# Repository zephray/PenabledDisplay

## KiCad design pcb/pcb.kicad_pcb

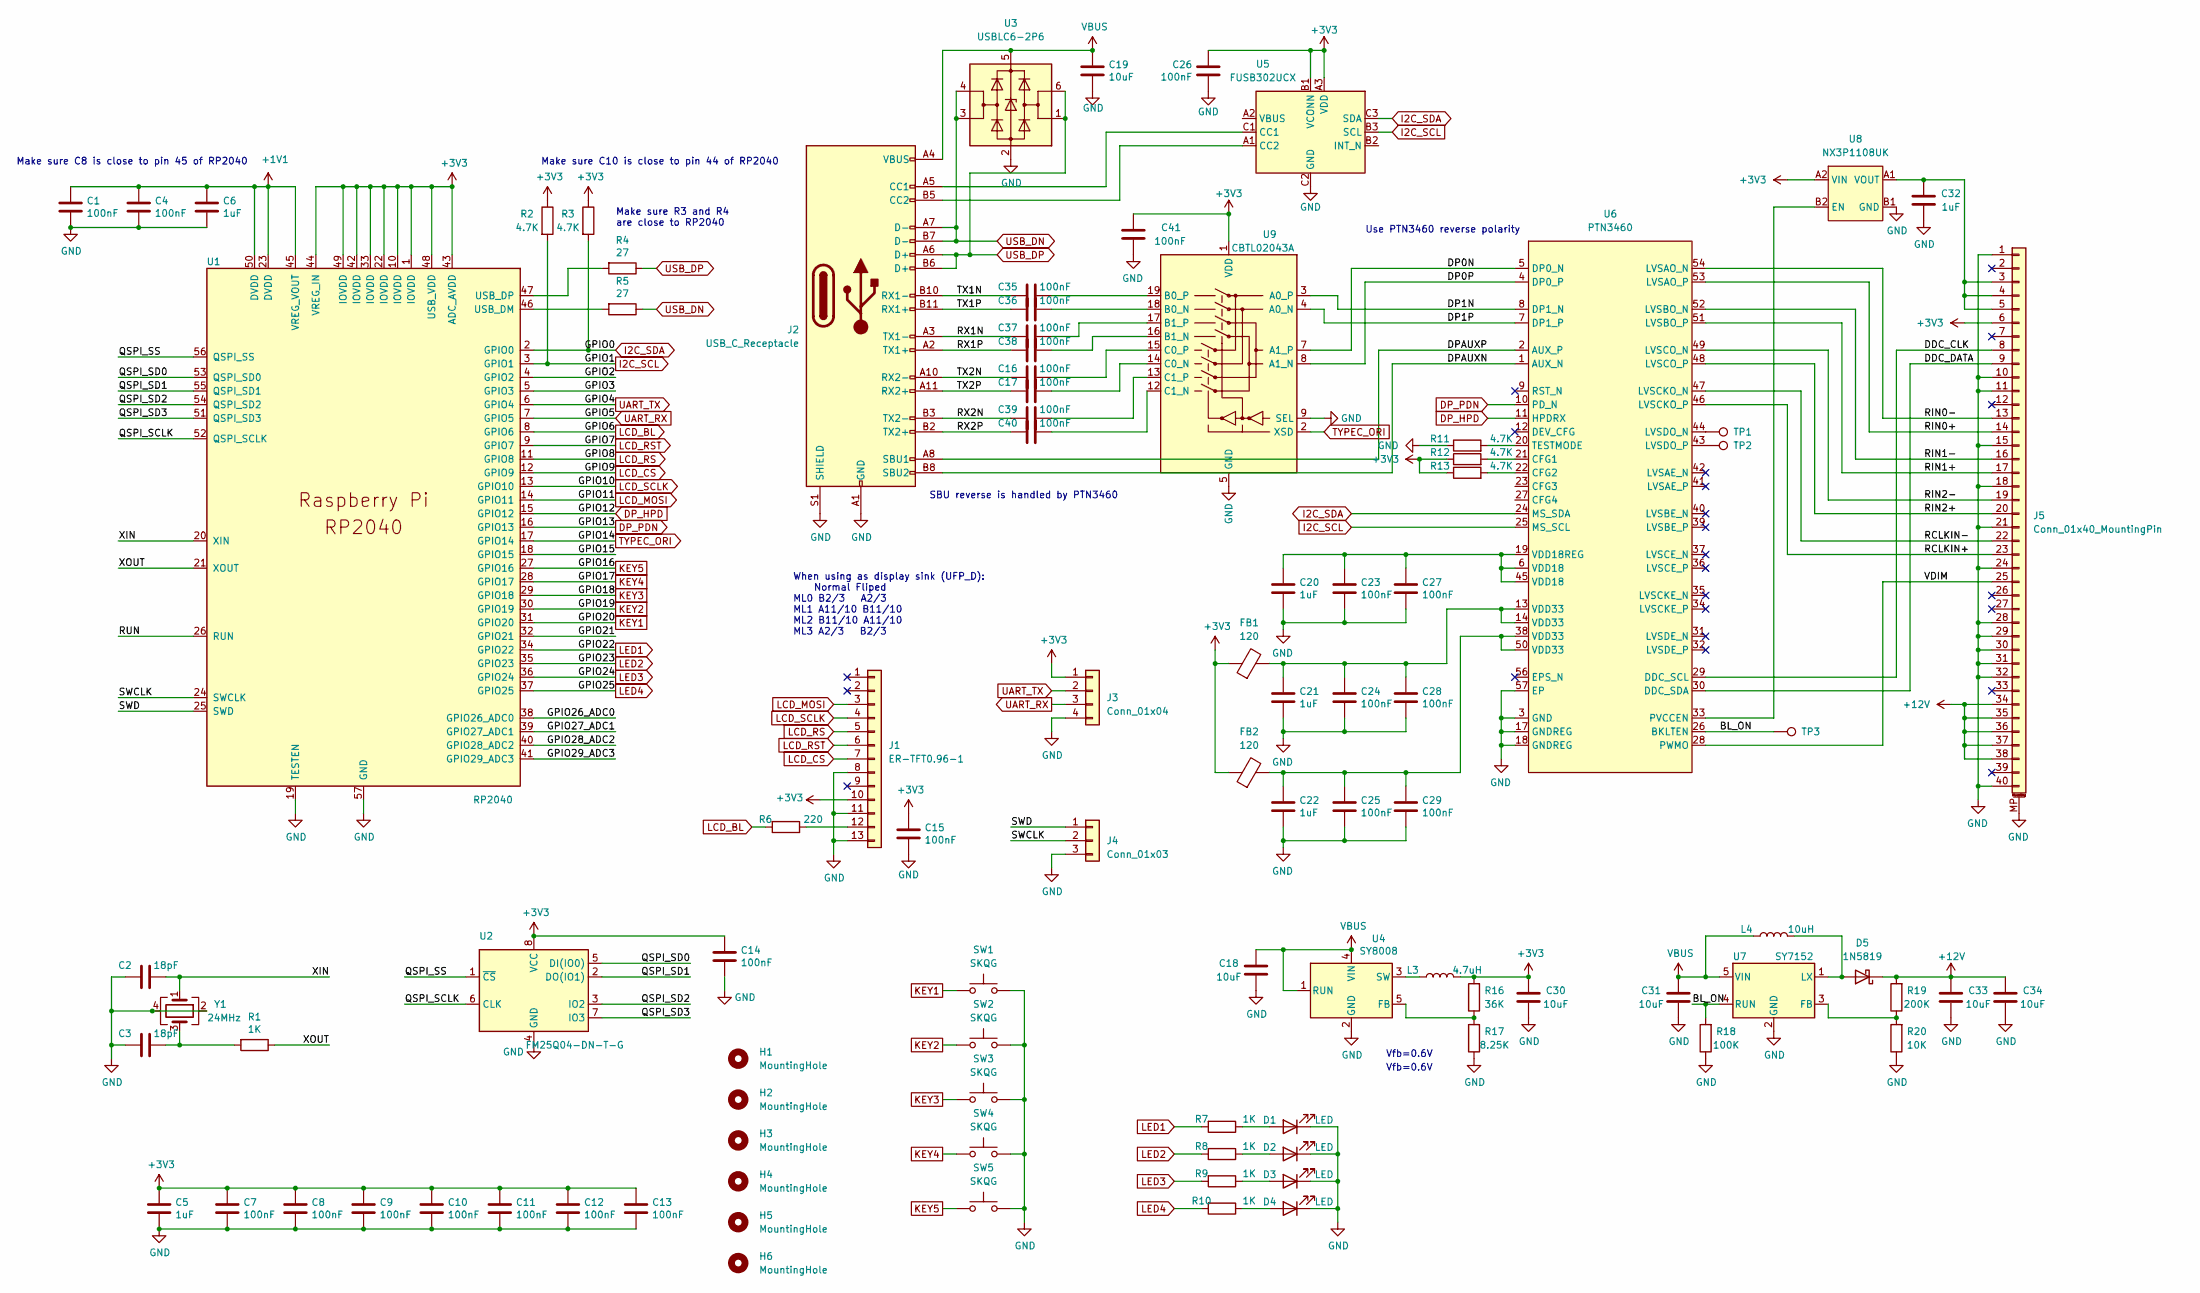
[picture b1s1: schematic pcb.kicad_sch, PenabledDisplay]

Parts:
C1, C4, C7, C8, C9, C10, C11, C12, C13, C14, C15, C16, C17, C23, C24, C25, C26, C27, C28, C29, C35, C36, C37, C38, C39, C40, C41: 100nF; C_0402_1005Metric
C2, C3: 18pF; C_0402_1005Metric
C5, C6, C20, C21, C22, C32: 1uF; C_0402_1005Metric
C18, C19, C30, C31, C33, C34: 10uF; C_0603_1608Metric
D1, D2, D3, D4: LED; LED_0603_1608Metric
D5: 1N5819; D_SOD-123
FB1, FB2: 120; L_0603_1608Metric
H1, H2: MountingHole; MountingHole_2.2mm_M2_DIN965_Pad
H3: MountingHole; MountingHole_2.2mm_M2_DIN965
H4, H5: MountingHole; MountingHole_2.7mm_M2.5_DIN965_Pad
H6: MountingHole; MountingHole_1.7mm
J1: ER-TFT0.96-1; FPC_13_B
J2: USB_C_Receptacle; USB_C_Receptacle_Amphenol_12401548E4-2A
J3: Conn_01x04; PinHeader_1x04_P1.27mm_Vertical
J4: Conn_01x03; PinHeader_1x03_P2.54mm_Vertical
J5: Conn_01x40_MountingPin; Hirose_FH12-40S-0.5SH_1x40-1MP_P0.50mm_Horizontal_Reversed
L3: 4.7uH; L_Vishay_IHLP-1212
L4: 10uH; L_Vishay_IHLP-1616
R1, R7, R8, R9, R10: 1K; R_0402_1005Metric
R2, R3, R11, R12, R13: 4.7K; R_0402_1005Metric
R4, R5: 27; R_0402_1005Metric
R6: 220; R_0402_1005Metric
R16: 36K; R_0402_1005Metric
R17: 8.25K; R_0402_1005Metric
R18: 100K; R_0402_1005Metric
R19: 200K; R_0402_1005Metric
R20: 10K; R_0402_1005Metric
SW1, SW2, SW3, SW4, SW5: SKQG; SW_SPST_SKQG_WithStem
TP1, TP2, TP3: TestPoint; TestPoint_Pad_D1.0mm
U1: RP2040; QFN-56-1EP_7x7mm_P0.4mm_EP5.6x5.6mm_ThermalVias
U2: FM25Q04-DN-T-G; DFN-8-1EP_3x2mm_P0.5mm_EP1.36x1.46mm
U3: USBLC6-2P6; SOT-666
U4: SY8008; TSOT-23-5
U5: FUSB302UCX; WLP-9_1.448x1.468mm_Layout3x3_P0.4mm_Ball0.27mm_Pad0.25mm
U6: PTN3460; QFN-56-1EP_7x7mm_P0.4mm_EP5.6x5.6mm
U7: SY7152; TSOT-23-6
U8: NX3P1108UK; WLCSP-4-X1-WLB0909-4_0.89x0.89mm_P0.5mm
U9: CBTL02043A; WQFN-20-1EP_2.5x4.5mm_P0.5mm_EP1x2.9mm
Y1: 24MHz; Oscillator_SMD_Abracon_ASE-4Pin_3.2x2.5mm

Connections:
+1V1: C1.1, C4.1, C6.1, U1.23 (DVDD), U1.45 (VREG_VOUT), U1.50 (DVDD)
+3V3: C5.1, C7.1, C8.1, C9.1, C10.1, C11.1, C12.1, C13.1, C14.1, C15.1, C26.1, C30.2, C41.1, FB1.1, FB2.1, J1.10, J3.1, J5.6, L3.2, R2.1, R3.1, R12.1, R13.1, R16.2, U1.1 (IOVDD), U1.10 (IOVDD), U1.22 (IOVDD), U1.33 (IOVDD), U1.42 (IOVDD), U1.43 (ADC_AVDD), U1.44 (VREG_IN), U1.48 (USB_VDD), U1.49 (IOVDD), U2.8 (VCC), U5.A3 (VDD), U5.B1 (VCONN), U8.A2 (VIN), U9.1 (VDD), U9.6 (VDD), U9.10 (VDD)
+12V: C33.2, C34.2, D5.1 (K), J5.34, J5.35, J5.36, J5.37, J5.38, R19.2
/BL_ON: R18.2, TP3.1, U6.26 (BKLTEN), U7.4 (RUN)
/DDC_CLK: J5.8, U6.29 (DDC_SCL)
/DDC_DATA: J5.9, U6.30 (DDC_SDA)
/DP0N: U6.5 (DP0_N), U9.7 (A1_P)
/DP0P: U6.4 (DP0_P), U9.8 (A1_N)
/DP1N: U6.8 (DP1_N), U9.3 (A0_P)
/DP1P: U6.7 (DP1_P), U9.4 (A0_N)
/DPAUXN: J2.B8 (SBU2), U6.1 (AUX_N)
/DPAUXP: J2.A8 (SBU1), U6.2 (AUX_P)
/GPIO2: U1.4 (GPIO2)
/GPIO3: U1.5 (GPIO3)
/GPIO15: U1.18 (GPIO15)
/GPIO21: U1.32 (GPIO21)
/GPIO26_ADC0: U1.38 (GPIO26_ADC0)
/GPIO27_ADC1: U1.39 (GPIO27_ADC1)
/GPIO28_ADC2: U1.40 (GPIO28_ADC2)
/GPIO29_ADC3: U1.41 (GPIO29_ADC3)
/QSPI_SCLK: U1.52 (QSPI_SCLK), U2.6 (CLK)
/QSPI_SD0: U1.53 (QSPI_SD0), U2.5 (DI(IO0))
/QSPI_SD1: U1.55 (QSPI_SD1), U2.2 (DO(IO1))
/QSPI_SD2: U1.54 (QSPI_SD2), U2.3 (IO2)
/QSPI_SD3: U1.51 (QSPI_SD3), U2.7 (IO3)
/QSPI_SS: U1.56 (QSPI_SS), U2.1 (~CS)
/RCLKIN+: J5.23, U6.46 (LVSCKO_P)
/RCLKIN-: J5.22, U6.47 (LVSCKO_N)
/RIN0+: J5.14, U6.53 (LVSAO_P)
/RIN0-: J5.13, U6.54 (LVSAO_N)
/RIN1+: J5.17, U6.51 (LVSBO_P)
/RIN1-: J5.16, U6.52 (LVSBO_N)
/RIN2+: J5.20, U6.48 (LVSCO_P)
/RIN2-: J5.19, U6.49 (LVSCO_N)
/RUN: U1.26 (RUN)
/RX1N: C37.1, J2.A3 (TX1-)
/RX1P: C38.1, J2.A2 (TX1+)
/RX2N: C39.1, J2.B3 (TX2-)
/RX2P: C40.1, J2.B2 (TX2+)
/SWCLK: J4.2, U1.24 (SWCLK)
/SWD: J4.1, U1.25 (SWD)
/TX1N: C35.1, J2.B10 (RX1-)
/TX1P: C36.1, J2.B11 (RX1+)
/TX2N: C16.1, J2.A10 (RX2-)
/TX2P: C17.1, J2.A11 (RX2+)
/VDIM: J5.25, U6.28 (PWMO)
/XIN: C2.1, U1.20 (XIN), Y1.1
/XOUT: R1.1, U1.21 (XOUT)
DP_HPD: U1.15 (GPIO12), U6.11 (HPDRX)
DP_PDN: U1.16 (GPIO13), U6.10 (PD_N)
GND: C1.2, C2.2, C3.2, C4.2, C5.2, C6.2, C7.2, C8.2, C9.2, C10.2, C11.2, C12.2, C13.2, C14.2, C15.2, C18.1, C19.2, C20.2, C21.2, C22.2, C23.2, C24.2, C25.2, C26.2, C27.2, C28.2, C29.2, C30.1, C31.1, C32.1, C33.1, C34.1, C41.2, D1.1 (K), D2.1 (K), D3.1 (K), D4.1 (K), J1.8, J1.11, J1.13, J2.A1 (GND), J2.A12 (GND), J2.B1 (GND), J2.B12 (GND), J2.S1 (SHIELD), J3.4, J4.3, J5.1, J5.10, J5.11, J5.15, J5.18, J5.21, J5.24, J5.28, J5.29, J5.30, J5.31, J5.32, J5.40, J5.MP (MountPin), R11.1, R17.1, R18.1, R20.1, SW1.2, SW2.2, SW3.2, SW4.2, SW5.2, U1.19 (TESTEN), U1.57 (GND), U2.4 (GND), U3.2 (GND), U4.2 (GND), U5.C2 (GND), U6.3 (GND), U6.17 (GNDREG), U6.18 (GNDREG), U6.57 (EP), U7.2 (GND), U8.B1 (GND), U9.5 (GND), U9.9 (SEL), U9.11 (GND), U9.20 (GND), U9.21 (GND), Y1.2, Y1.4
I2C_SCL: R2.2, U1.3 (GPIO1), U5.B3 (SCL), U6.25 (MS_SCL)
I2C_SDA: R3.2, U1.2 (GPIO0), U5.C3 (SDA), U6.24 (MS_SDA)
KEY1: SW1.1, U1.31 (GPIO20)
KEY2: SW2.1, U1.30 (GPIO19)
KEY3: SW3.1, U1.29 (GPIO18)
KEY4: SW4.1, U1.28 (GPIO17)
KEY5: SW5.1, U1.27 (GPIO16)
LCD_BL: R6.2, U1.8 (GPIO6)
LCD_CS: J1.7, U1.12 (GPIO9)
LCD_MOSI: J1.3, U1.14 (GPIO11)
LCD_RS: J1.5, U1.11 (GPIO8)
LCD_RST: J1.6, U1.9 (GPIO7)
LCD_SCLK: J1.4, U1.13 (GPIO10)
LED1: R7.2, U1.34 (GPIO22)
LED2: R8.2, U1.35 (GPIO23)
LED3: R9.2, U1.36 (GPIO24)
LED4: R10.2, U1.37 (GPIO25)
unnamed: C3.1, R1.2, Y1.3
unnamed: C16.2, U9.15 (C0_P)
unnamed: C17.2, U9.14 (C0_N)
unnamed: C20.1, C23.1, C27.1, U6.6 (VDD18), U6.19 (VDD18REG), U6.45 (VDD18)
unnamed: C21.1, C24.1, C28.1, FB1.2, U6.13 (VDD33), U6.14 (VDD33)
unnamed: C22.1, C25.1, C29.1, FB2.2, U6.38 (VDD33), U6.50 (VDD33)
unnamed: C32.2, J5.3, J5.4, J5.5, U8.A1 (VOUT)
unnamed: C35.2, U9.19 (B0_P)
unnamed: C36.2, U9.18 (B0_N)
unnamed: C37.2, U9.17 (B1_P)
unnamed: C38.2, U9.16 (B1_N)
unnamed: C39.2, U9.13 (C1_P)
unnamed: C40.2, U9.12 (C1_N)
unnamed: D1.2 (A), R7.1
unnamed: D2.2 (A), R8.1
unnamed: D3.2 (A), R9.1
unnamed: D4.2 (A), R10.1
unnamed: D5.2 (A), L4.2, U7.1 (LX)
unnamed: J1.12, R6.1
unnamed: J2.A5 (CC1), U5.C1 (CC1)
unnamed: J2.B5 (CC2), U5.A1 (CC2)
unnamed: L3.1, U4.3 (SW)
unnamed: R4.2, U1.47 (USB_DP)
unnamed: R5.2, U1.46 (USB_DM)
unnamed: R11.2, U6.20 (TESTMODE)
unnamed: R12.2, U6.21 (CFG1)
unnamed: R13.2, U6.22 (CFG2)
unnamed: R16.1, R17.2, U4.5 (FB)
unnamed: R19.1, R20.2, U7.3 (FB)
unnamed: TP1.1, U6.44 (LVSDO_N)
unnamed: TP2.1, U6.43 (LVSDO_P)
unnamed: U6.33 (PVCCEN), U8.B2 (EN)
TYPEC_ORI: U1.17 (GPIO14), U9.2 (XSD)
UART_RX: J3.3, U1.7 (GPIO5)
UART_TX: J3.2, U1.6 (GPIO4)
USB_DN: J2.A7 (D-), J2.B7 (D-), R5.1, U3.3 (I/O2), U3.4 (I/O2)
USB_DP: J2.A6 (D+), J2.B6 (D+), R4.1, U3.1 (I/O1), U3.6 (I/O1)
VBUS: C18.2, C19.1, C31.2, J2.A4 (VBUS), J2.A9 (VBUS), J2.B4 (VBUS), J2.B9 (VBUS), L4.1, U3.5 (VBUS), U4.1 (RUN), U4.4 (VIN), U7.5 (VIN)

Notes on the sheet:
Vfb=0.6V
Make sure C8 is close to pin 45 of RP2040
Use PTN3460 reverse polarity
SBU reverse is handled by PTN3460
Make sure C10 is close to pin 44 of RP2040
Make sure R3 and R4 are close to RP2040
When using as display sink (UFP_D): Normal Fliped ML0 B2/3 A2/3 ML1 A11/10 B11/10 ML2 B11/10 A11/10 ML3 A2/3 B2/3

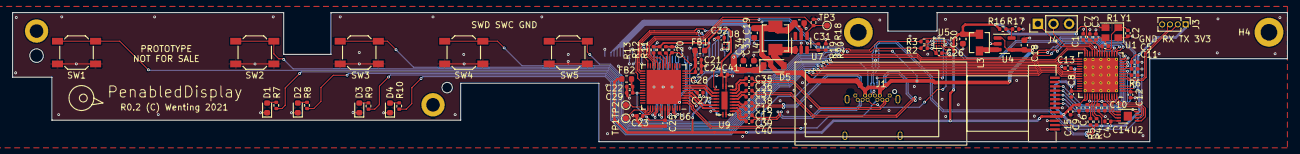
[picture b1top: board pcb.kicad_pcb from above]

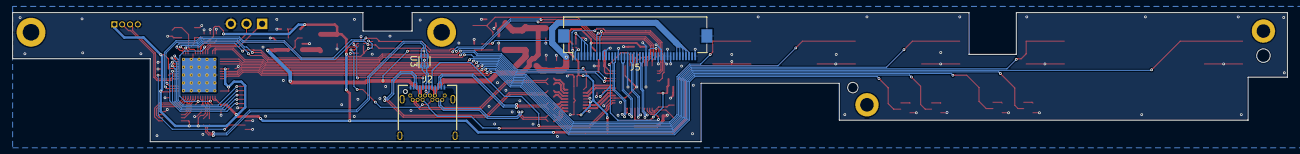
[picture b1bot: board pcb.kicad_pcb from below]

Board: 4 copper layers, 207.4 x 21.0 mm, 97 parts (3 on the bottom side), 97 nets.

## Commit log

2021-03-11 PCB Rev 0.1
2021-04-05 fw: initial lcd and pd support
2021-12-24 fw: pd dp alt mode working
2022-04-03 pcb: rev 0.2
